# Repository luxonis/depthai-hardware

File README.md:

# DepthAI Open Source Hardware

This repository contains Luxonis open sourced baseboards, including the DepthAI OpenCV AI Kits, and contains Altium design files, documentation, and pictures. This repository is for anyone interested in developing with the OAK SoM or anyone interested in understanding more about the embedded hardware that powers DepthAI. An open source, community KiCad folder is also available for sharing KiCad based designs and components.

The designs are Dual Licensed under [MIT](LICENSE) or [KiCad Libraries License](LICENSE.KiCad.md)

# POE Designs

## [OAK-D-POE | SJ2088POE](https://github.com/luxonis/depthai-hardware/tree/master/SJ2088POE_PoE_Board)

This board is the basis for the OAK-D-POE.  And it is the equivalent of the BW1098OBC/BW1098OAK, but with POE instead of USB.  So 3 onboard cameras (1x onboard IMX378 12MP autofocus color camera, 2x global shutter grayscale for stereo depth), with the stereo baseline being 7.5cm (just like BW1098OBC/BW1098OAK/OAK-D).

This design is in progress.  When complete it will support the DepthAI API over Ethernet, and some additional features like direct RTSP streaming.

## [OAK-1-POE | SJ2096POE](https://github.com/luxonis/depthai-hardware/tree/master/SJ2096POE_R0M0E0)

This is the basis for OAK-1-POE.  It is the equivalent of the BK1096_OAK, with with POE instead of USB.  So 1x onboard IMX378 12MP autofocus color camera.

This design is in progress.  When complete it will support the DepthAI API over Ethernet, and some additional features like direct RTSP streaming.

## [BW2098POE](https://github.com/luxonis/depthai-hardware/tree/master/BW2098POE_PoE_Board)
The [BW2098POE repository](https://github.com/luxonis/depthai-hardware/tree/master/BW2098POE_PoE_Board) contains open hardware designed by Luxonis, and meant to be used as a baseboard for the [Luxonis](https://www.luxonis.com/depthai) BW2099 OAK SoM. The BW2098POE baseboard offers full 802.3af, Class 3 PoE compliance with 1000BASE-T speeds, along with user-selectable external power from a 5V barrel jack. The Luxonis BW0249 12MP RGB camera module can be connected via the 26-pin FFC interface, which exposes a 4-lane MIPI CSI-2 channel directly into the Myriad X on the BW2099 module for processing. Data can also be streamed to a host via USB 3.1 Gen1 (Type-C). Finally, the BW2098POE board exposes boot selection switches, allowing the end user to boot the BW2099 module from USB or the on-board eMMC or NOR flash.

# Integrated Raspberry Pi Designs

## [DM1097](https://github.com/luxonis/depthai-hardware/tree/master/DM1097_DepthAI_Compute_Module_4#dm1097_r0m0e0-depthai-for-compute-module-4)
The [DM1097](https://github.com/luxonis/depthai-hardware/tree/master/DM1097_DepthAI_Compute_Module_4#dm1097_r0m0e0-depthai-for-compute-module-4) contains the design files for DepthAI with an integrated/onboard [Raspberry Pi Compute Module 4](https://www.raspberrypi.org/products/compute-module-4/?variant=raspberry-pi-cm4001000).
The DM1097 combines a host and the Luxonis OAK SoM to allow for fully integrated solution for real-time spatial AI. It is effectively the same as the BW1097, below, but with a Pi 4 computer module instead of a Pi 3 compute module.

## [BW1097](BW1097_DepthAI_Compute_Module)
The [BW1097 repository](/BW1097_DepthAI_Compute_Module) contains open hardware designed by Luxonis, and meant to be used as a baseboard for the [Luxonis](https://www.luxonis.com/depthai) BW1099 OAK SoM and the [Raspberry Pi Compute Module 3+](https://www.raspberrypi.org/products/compute-module-3-plus/). Based on the Raspberry PI CMIO board, the BW1097 combines a host and the Luxonis OAK SoM to allow for fully integrated solution for real-time spatial AI.

# USB Designs

## [OAK-D | BW1098OAK](https://github.com/luxonis/depthai-hardware/tree/master/BW1098OAK_USB3C#bw1098oak-usb3c-baseboard)

This board is used in the depthai product known as the OpenCV AI Kit with Depth, OAK-D:

## [BW1098OBC](BW1098OBC_DepthAI_USB3C)
The [BW1098OBC repository](BW1098OBC_DepthAI_USB3C) contains open hardware designed by Luxonis, and meant to be used as a baseboard for the [Luxonis](https://www.luxonis.com/depthai) BW1099 OAK SoM. The BW1098OBC baseboard has three on-board cameras which implement stereo and RGB vision, piped directly into the OAK SoM for depth and AI processing. The data is then output to a host via USB 3.1 Gen1 (Type-C).

# USB designs with attachable FFC camera boards

The 1090 is our updated version from the common issues customers have had with BW1098FFC. (We will keep selling the 1098FFC, for folks who have that connector type.)
Improvements/changes:

- More robust mechanical connection (a LOT more robust)
- ESD protection added.
- Standardized pinout (All 3 camera connectors have the same pinout - meaning that mix/match can be done using 2x 2-lane MIPI and 1x 4-lane MIPI)
- Capability to use with ArduCam cameras w/out an adapter board (including clock sync and trigger sync).

Below is a flow-chart showing the evolution of this design over time based on customer feedback/needs.

More information about each design can be found in corresponding repositories.

## [DM1090FFC](DM1090FFC_DepthAI_USB3)

The [DM1090FFC repository](DM1090FFC_DepthAI_USB3) contains open hardware designed by Luxonis, and meant to be used as a baseboard for the [Luxonis](https://www.luxonis.com/depthai) BW1099 OAK SoM. The DM1090FFC baseboard has three FFC interfaces which allow for two [DM0250TG](DM0250TG_DepthAI_Mono_Camera) camera modules (stereo pair) and one [DM0249](DM0249_DepthAI_RGB_Camera) RGB camera module.
Besides Luxonis camera modules, several Arducam CCMs can be connected to [DM1090FFC](DM1090FFC_DepthAI_USB3).
Please note that only revision R1 and above (R1M1E1) ([DM0250TG](DM0250TG_DepthAI_Mono_Camera) and [DM0249](DM0249_DepthAI_RGB_Camera)) cameras with 26-pin FFC connectors can be connected to [DM1090FFC](DM1090FFC_DepthAI_USB3).

## [BW1094](BW1094_DepthAI_HAT)
The [BW1094 repository](BW1094_DepthAI_HAT) contains open hardware designed by Luxonis, and meant to be used as a baseboard for the [Luxonis](https://www.luxonis.com/depthai) BW1099 OAK SoM and as a HAT for the [RPi "B" models](https://www.raspberrypi.org/products/). The BW1094 baseboard has three FFC interfaces which allow for two [BG0250TG](BG0250TG_DepthAI_Mono_Camera) camera modules (stereo pair) and one [BG0249](BG0249_DepthAI_RGB_Camera) RGB camera module. The GPIO interface from the Raspberry Pi Model B variants is passed through the BW1094 with the exception of the 5V pins, GND pins, and [BCM GPIO26 (pin 37)](https://www.raspberrypi.org/documentation/usage/gpio/), which is used as a way for the Raspberry Pi to reset the OAK SoM, parallel to the RST button.

## [BK1096](BK1096_OAK-1_Modular)
The [BK1096 repository](/BK1096_OAK-1_Modular) contains open hardware designed by Luxonis, and meant to be used as a baseboard for the [Luxonis](https://www.luxonis.com/depthai) BW1099 OAK SoM. The BK1096 baseboard offers a quick and simple way to add USB3 Type-C device power and connectivity, and a single 12MP RGB camera module to the OAK SoM.

# Cameras and Camera Adapter Boards

## [BG0249](BG0249_DepthAI_RGB_Camera)
The [BG0249 repository](BG0249_DepthAI_RGB_Camera) contains open hardware designed by Luxonis. The BW0249 is a carrier board for the Sunny A12N02A IMX378 camera module, and is designed to be compatible with the [BW1094](BW1094_DepthAI_HAT) and [BW1098FFC](BW1098FFC_DepthAI_USB3) baseboards. A 26-pin FFC is used to carry 5V power, 4-lane MIPI, I2C, and other control signals between the BW0249 and the controller baseboards.

## [BG0250TG](BG0250TG_DepthAI_Mono_Camera)
The [BG0250TG repository](BG0250TG_DepthAI_Mono_Camera) contains open hardware designed by Luxonis. The BW0250TG is a carrier board for the Sunny TG161B or AN01V32 OV9282 camera module, and is designed to be compatible with the [BW1094](BW1094_DepthAI_HAT) and [BW1098FFC](BW1098FFC_DepthAI_USB3) baseboards. A 20-pin FFC is used to carry 5V power, 2-lane MIPI, I2C, and other control signals between the BW0250TG and the controller baseboards. A single BG0250TG is typically paired with another to create a stereo camera pair.

## [BW0253_R0M0E0 Raspberry Pi HQ Cam Adapter Board](/BW0253_R0M0E0_RPIHQ_ADAPTER)

The [BW0253_R0M0E0](/BW0253_R0M0E0_RPIHQ_ADAPTER) is an adapter board to allow the [Raspberry Pi HQ camera](https://www.raspberrypi.org/products/raspberry-pi-high-quality-camera/) to physically interface to the DepthAI RGB camera port on the [BW1098FFC](https://github.com/luxonis/depthai-hardware/tree/master/BW1098FFC_DepthAI_USB3).

This allows using DepthAI with all sorts of lens combinations, including variable zoom, variable focus, and even [with a telescope](https://www.tomshardware.com/news/raspberry-pi-high-quality-camera-used-for-out-of-this-world-astrophotography).

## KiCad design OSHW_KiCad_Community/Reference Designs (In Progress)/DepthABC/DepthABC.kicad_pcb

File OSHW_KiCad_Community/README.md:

# DepthAI Open Source Hardware KiCad Community

An open source, community KiCad folder is also available for sharing KiCad based designs and components. 

## Contents

### Footprints

Contains entire *converted* altium luxonis-depthAI footprint library. Dimensions unconfirmed where noted. As they are checked they should be placed into the master library. Same goes for any footprints you create for a depthAI related design. 

### Schematic Libraries

Kicad depthAI schematic symbols. All are correct, some are missing, many have not had their footprint checked and assigned (but all are available in footprints). Still, use KiCad libraries if you have the part - will already have a model and footprint associated. 

### Reference Designs (in progress)

For KiCad versions of the reference designs provided in altium or their derivatives. Contains complete BW1098OBC-USBC Schematic as well as the WIP BW1098-ABC, a new collaboration with Chris Gammell.

### SoMs
this folder contains work on the 100 pin SoM connector using v6 of KiCad. The footprints folder and schematic libraries folders have it for v5. Going forward save v6 symbols with _v6 at the end so they can be differentiated (kicad v5 cannot use v6 footprints and symbols)
-->still need BW2099 Symbol
### Note: 

KiCad versions of reference designs, footprint/schematic libraries are still very much in the early stages. Once a few designs are complete and more footprints are confirmed, etc, it will be noted which parts of this directory are complete and may be used for reference while others will be marked WIP. For now assume all subdirectories to be in progress unless otherwise noted but please feel free to fork and add what you can to help out with the depthAI community.

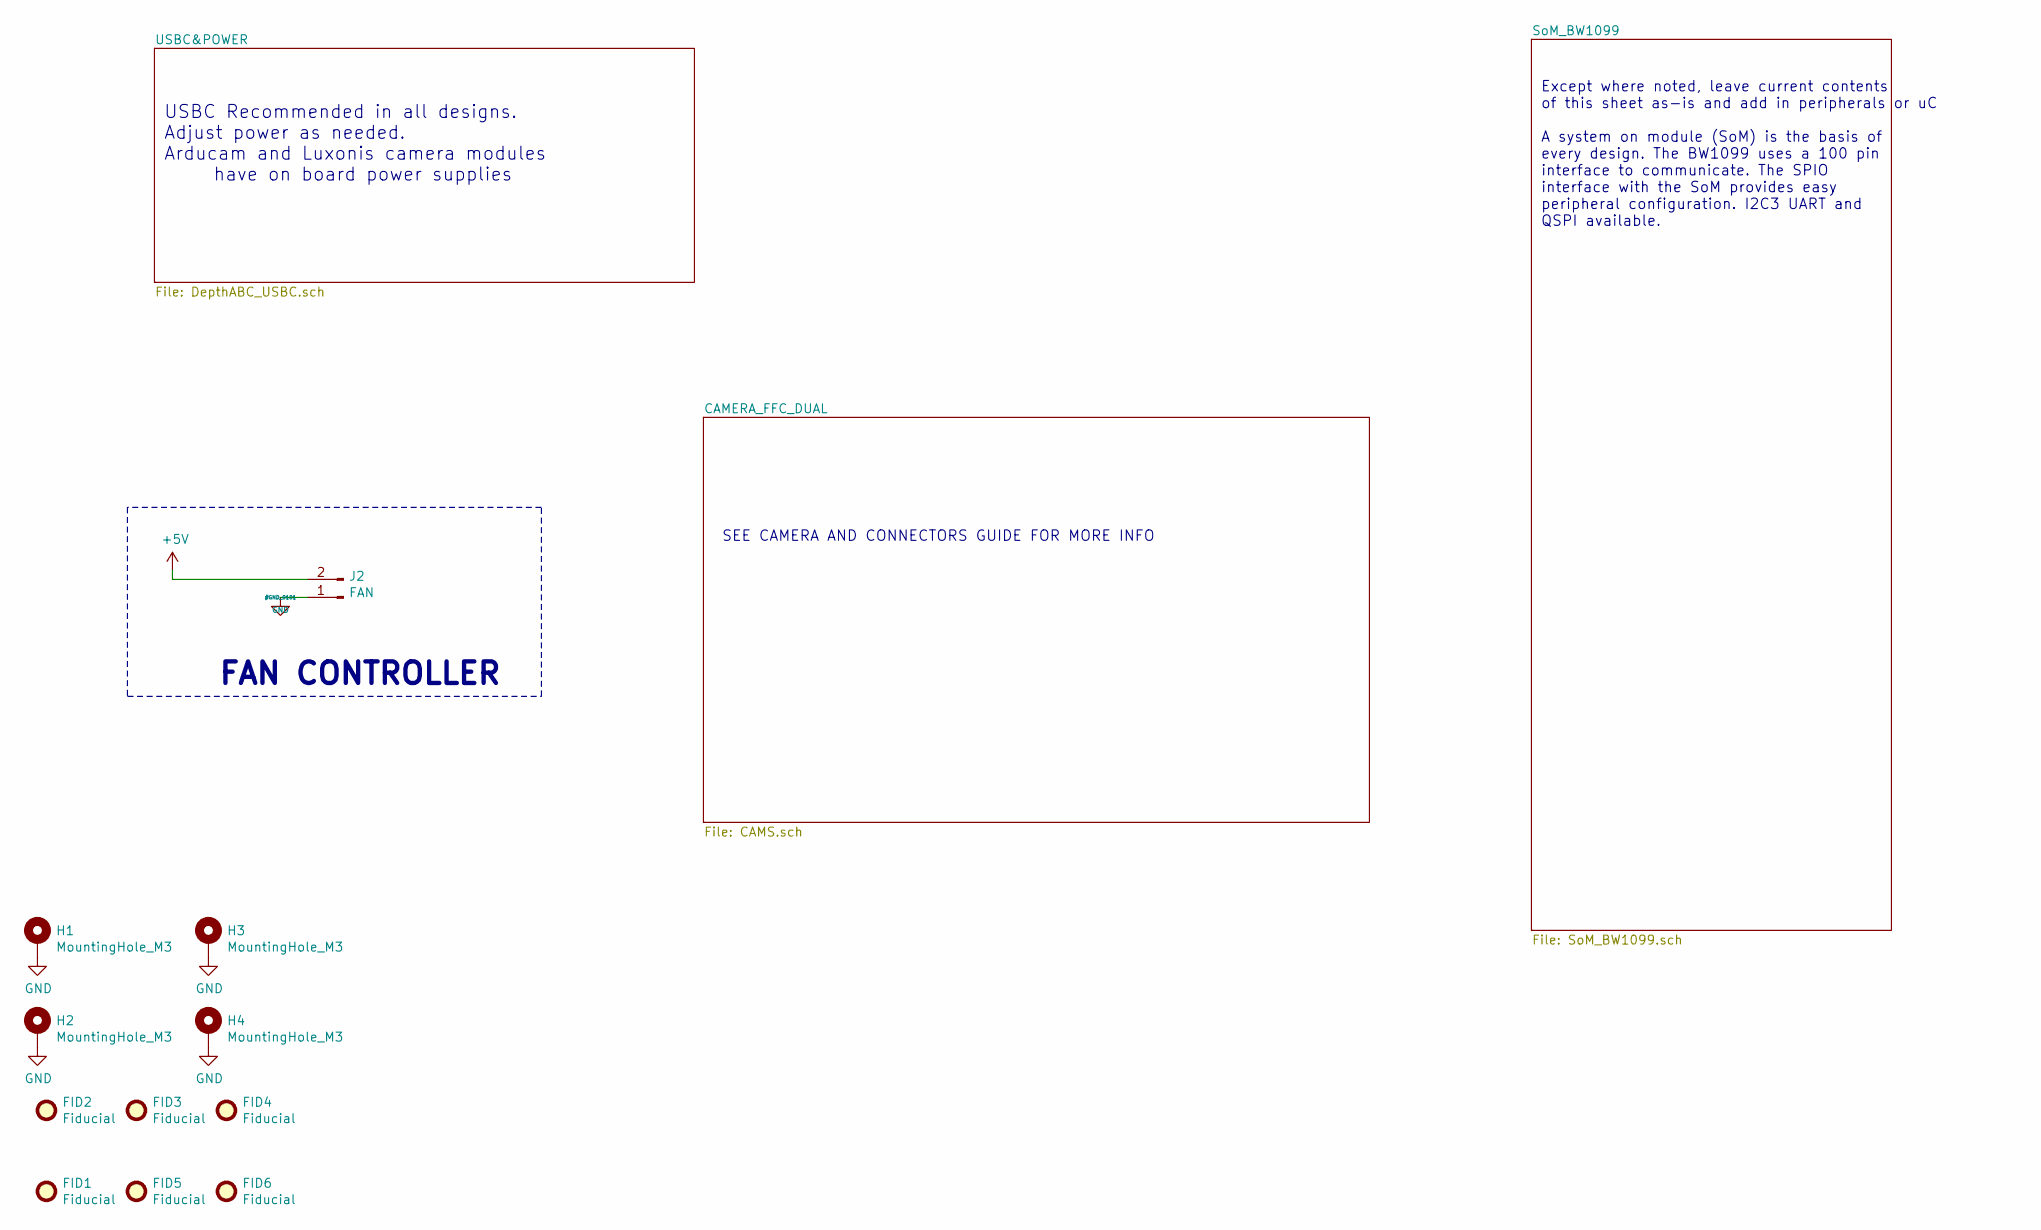
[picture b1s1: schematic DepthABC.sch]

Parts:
FID1, FID2, FID3, FID4, FID5, FID6: Fiducial; Fiducial_1mm_Mask2mm
H1, H2, H3, H4: MountingHole_M3; MountingHole_3.2mm_M3_ISO7380_Pad
J2: FAN; PinHeader_1x02_P2.54mm_Vertical

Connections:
+5V: J2.2; also elsewhere on the board

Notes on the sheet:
SEE CAMERA AND CONNECTORS GUIDE FOR MORE INFO
Except where noted, leave current contents of this sheet as-is and add in peripherals or uC A system on module (SoM) is the basis of every design. The BW1099 uses a 100 pin interface to communicate. The SPIO interface with the SoM provides easy peripheral configuration. I2C3 UART and QSPI available.
USBC Recommended in all designs. Adjust power as needed. Arducam and Luxonis camera modules have on board power supplies
FAN CONTROLLER

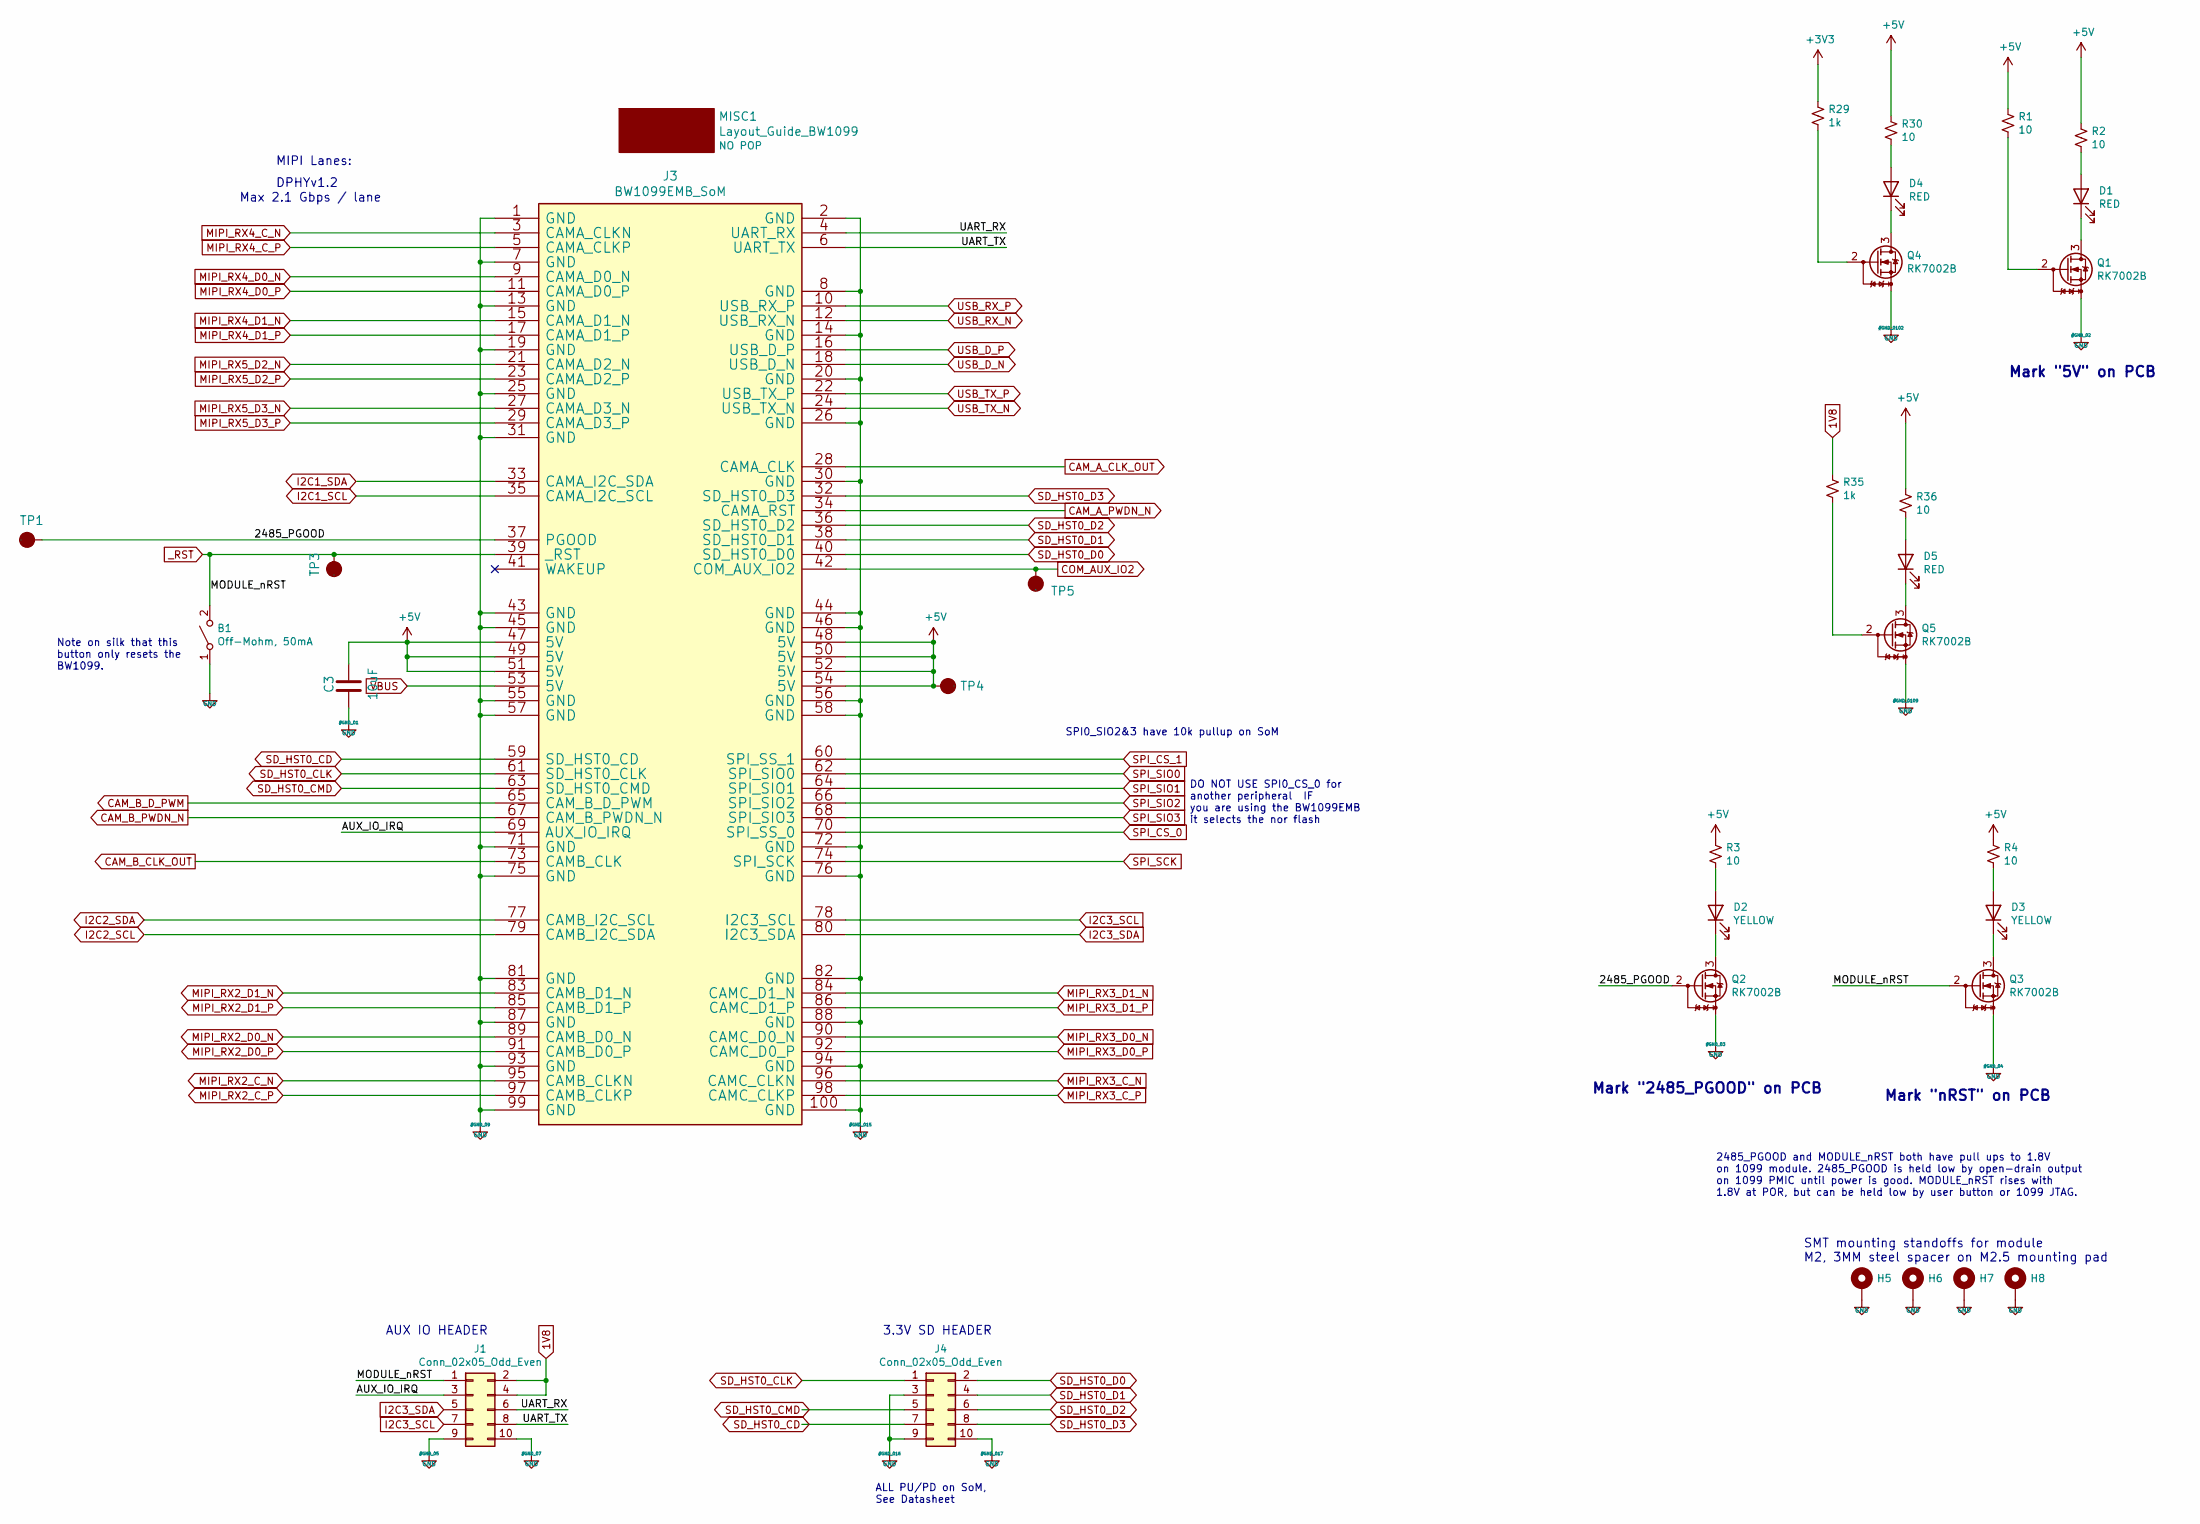
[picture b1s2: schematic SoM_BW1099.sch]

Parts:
B1: Off-Mohm, 50mA; SW_PTS636_SM43J_SMTR_LFS; MPN1 PTS636
C3: 10uF; C_0603_1608Metric; Voltage Rating 6.3V; MPN1 C0603C106M8PAC7867
D1, D4, D5: RED; LED_0805_2012Metric; MPN1 APT2012SRCPRV
D2, D3: YELLOW; LED_0805_2012Metric; MPN1 APT2012SYCK/J3-PRV
H5, H6, H7, H8: MountingHole_Pad; Mounting_Wuerth_WA-SMSI-M2_H3mm_9774030243; MPN1 9774030243R
J1, J4: Conn_02x05_Odd_Even; PinSocket_2x05_P2.54mm_Vertical_SMD
J3: BW1099EMB_SoM; DF40HC(3.0)-100DS-0.4V(58); MPN1 DF40HC(3.0)-100DS-0.4V(58)
MISC1: Layout_Guide_BW1099; BW1099_Layout_Guide
Q1, Q2, Q3, Q4, Q5: RK7002B; SOT-23; Voltage Rating 60V 250mA
R1, R2, R3, R4, R30, R36: 10; R_0603_1608Metric; Voltage Rating 1/10W; MPN1 ESR03EZPF10R0
R29, R35: 1k; R_0603_1608Metric; Voltage Rating 1/10W; MPN1 SG73S1JTTD1001F
TP1, TP3, TP4, TP5: TestPoint_Pad_D2.0mm

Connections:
1V8: J1.2, J1.4, R35.1; also elsewhere on the board
+5V: C3.2, J3.47 (5V), J3.48 (5V), J3.49 (5V), J3.50 (5V), J3.51 (5V), J3.52 (5V), J3.54 (5V), R1.1, R2.1, R3.1, R4.1, R30.1, R36.1, TP4.1; also elsewhere on the board
/SoM_BW1099/2485_PGOOD: J3.37 (PGOOD), Q2.2 (G), TP1.1
/SoM_BW1099/AUX_IO_IRQ: J1.3, J3.69 (AUX_IO_IRQ)
/SoM_BW1099/UART_RX: J1.6, J3.4 (UART_RX)
/SoM_BW1099/UART_TX: J1.8, J3.6 (UART_TX)
CAM_A_CLK_OUT: J3.28 (CAMA_CLK); also elsewhere on the board
CAM_A_PWDN_N: J3.34 (CAMA_RST); also elsewhere on the board
CAM_B_CLK_OUT: J3.73 (CAMB_CLK); also elsewhere on the board
CAM_B_D_PWM: J3.65 (CAM_B_D_PWM); also elsewhere on the board
CAM_B_PWDN_N: J3.67 (CAM_B_PWDN_N); also elsewhere on the board
COM_AUX_IO2: J3.42 (COM_AUX_IO2), TP5.1; also elsewhere on the board
I2C1_SCL: J3.35 (CAMA_I2C_SCL); also elsewhere on the board
I2C1_SDA: J3.33 (CAMA_I2C_SDA); also elsewhere on the board
I2C2_SCL: J3.79 (CAMB_I2C_SDA); also elsewhere on the board
I2C2_SDA: J3.77 (CAMB_I2C_SCL); also elsewhere on the board
I2C3_SCL: J1.7, J3.78 (I2C3_SCL)
I2C3_SDA: J1.5, J3.80 (I2C3_SDA)
MIPI_RX2_C_N: J3.95 (CAMB_CLKN); also elsewhere on the board
MIPI_RX2_C_P: J3.97 (CAMB_CLKP); also elsewhere on the board
MIPI_RX2_D0_N: J3.89 (CAMB_D0_N); also elsewhere on the board
MIPI_RX2_D0_P: J3.91 (CAMB_D0_P); also elsewhere on the board
MIPI_RX2_D1_N: J3.83 (CAMB_D1_N); also elsewhere on the board
MIPI_RX2_D1_P: J3.85 (CAMB_D1_P); also elsewhere on the board
MIPI_RX3_C_N: J3.96 (CAMC_CLKN); also elsewhere on the board
MIPI_RX3_C_P: J3.98 (CAMC_CLKP); also elsewhere on the board
MIPI_RX3_D0_N: J3.90 (CAMC_D0_N); also elsewhere on the board
MIPI_RX3_D0_P: J3.92 (CAMC_D0_P); also elsewhere on the board
MIPI_RX3_D1_N: J3.84 (CAMC_D1_N); also elsewhere on the board
MIPI_RX3_D1_P: J3.86 (CAMC_D1_P); also elsewhere on the board
MIPI_RX4_C_N: J3.3 (CAMA_CLKN); also elsewhere on the board
MIPI_RX4_C_P: J3.5 (CAMA_CLKP); also elsewhere on the board
MIPI_RX4_D0_N: J3.9 (CAMA_D0_N); also elsewhere on the board
MIPI_RX4_D0_P: J3.11 (CAMA_D0_P); also elsewhere on the board
MIPI_RX4_D1_N: J3.15 (CAMA_D1_N); also elsewhere on the board
MIPI_RX4_D1_P: J3.17 (CAMA_D1_P); also elsewhere on the board
MIPI_RX5_D2_N: J3.21 (CAMA_D2_N); also elsewhere on the board
MIPI_RX5_D2_P: J3.23 (CAMA_D2_P); also elsewhere on the board
MIPI_RX5_D3_N: J3.27 (CAMA_D3_N); also elsewhere on the board
MIPI_RX5_D3_P: J3.29 (CAMA_D3_P); also elsewhere on the board
unnamed: D1.1 (K), Q1.3 (D)
unnamed: D1.2 (A), R2.2
unnamed: D2.1 (K), Q2.3 (D)
unnamed: D2.2 (A), R3.2
unnamed: D3.1 (K), Q3.3 (D)
unnamed: D3.2 (A), R4.2
unnamed: D4.1 (K), Q4.3 (D)
unnamed: D4.2 (A), R30.2
unnamed: D5.1 (K), Q5.3 (D)
unnamed: D5.2 (A), R36.2
unnamed: Q1.2 (G), R1.2
unnamed: Q4.2 (G), R29.2
unnamed: Q5.2 (G), R35.2
SD_HST0_CD: J3.59 (SD_HST0_CD), J4.7; also elsewhere on the board
SD_HST0_CLK: J3.61 (SD_HST0_CLK), J4.1; also elsewhere on the board
SD_HST0_CMD: J3.63 (SD_HST0_CMD), J4.5; also elsewhere on the board
SD_HST0_D0: J3.40 (SD_HST0_D0), J4.2; also elsewhere on the board
SD_HST0_D1: J3.38 (SD_HST0_D1), J4.4; also elsewhere on the board
SD_HST0_D2: J3.36 (SD_HST0_D2), J4.6; also elsewhere on the board
SD_HST0_D3: J3.32 (SD_HST0_D3), J4.8; also elsewhere on the board
SPI_CS_0: J3.70 (SPI_SS_0); also elsewhere on the board
SPI_CS_1: J3.60 (SPI_SS_1); also elsewhere on the board
SPI_SCK: J3.74 (SPI_SCK); also elsewhere on the board
SPI_SIO0: J3.62 (SPI_SIO0); also elsewhere on the board
SPI_SIO1: J3.64 (SPI_SIO1); also elsewhere on the board
SPI_SIO2: J3.66 (SPI_SIO2); also elsewhere on the board
SPI_SIO3: J3.68 (SPI_SIO3); also elsewhere on the board
USB_D_N: J3.18 (USB_D_N); also elsewhere on the board
USB_D_P: J3.16 (USB_D_P); also elsewhere on the board
USB_RX_N: J3.12 (USB_RX_N); also elsewhere on the board
USB_RX_P: J3.10 (USB_RX_P); also elsewhere on the board
USB_TX_N: J3.24 (USB_TX_N); also elsewhere on the board
USB_TX_P: J3.22 (USB_TX_P); also elsewhere on the board
VBUS: J3.53 (5V); also elsewhere on the board
_RST: B1.2 (B), J1.1, J3.39 (_RST), Q3.2 (G), TP3.1; also elsewhere on the board

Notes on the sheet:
SMT mounting standoffs for module M2, 3MM steel spacer on M2.5 mounting pad
Mark "5V" on PCB
Mark "2485_PGOOD" on PCB
Mark "nRST" on PCB
AUX IO HEADER
3.3V SD HEADER
Note on silk that this button only resets the BW1099.
2485_PGOOD and MODULE_nRST both have pull ups to 1.8V on 1099 module. 2485_PGOOD is held low by open-drain output on 1099 PMIC until power is good. MODULE_nRST rises with 1.8V at POR, but can be held low by user button or 1099 JTAG.
DPHYv1.2
MIPI Lanes:
Max 2.1 Gbps / lane
SPI0_SIO2&3 have 10k pullup on SoM
DO NOT USE SPI0_CS_0 for another peripheral IF you are using the BW1099EMB it selects the nor flash
ALL PU/PD on SoM, See Datasheet

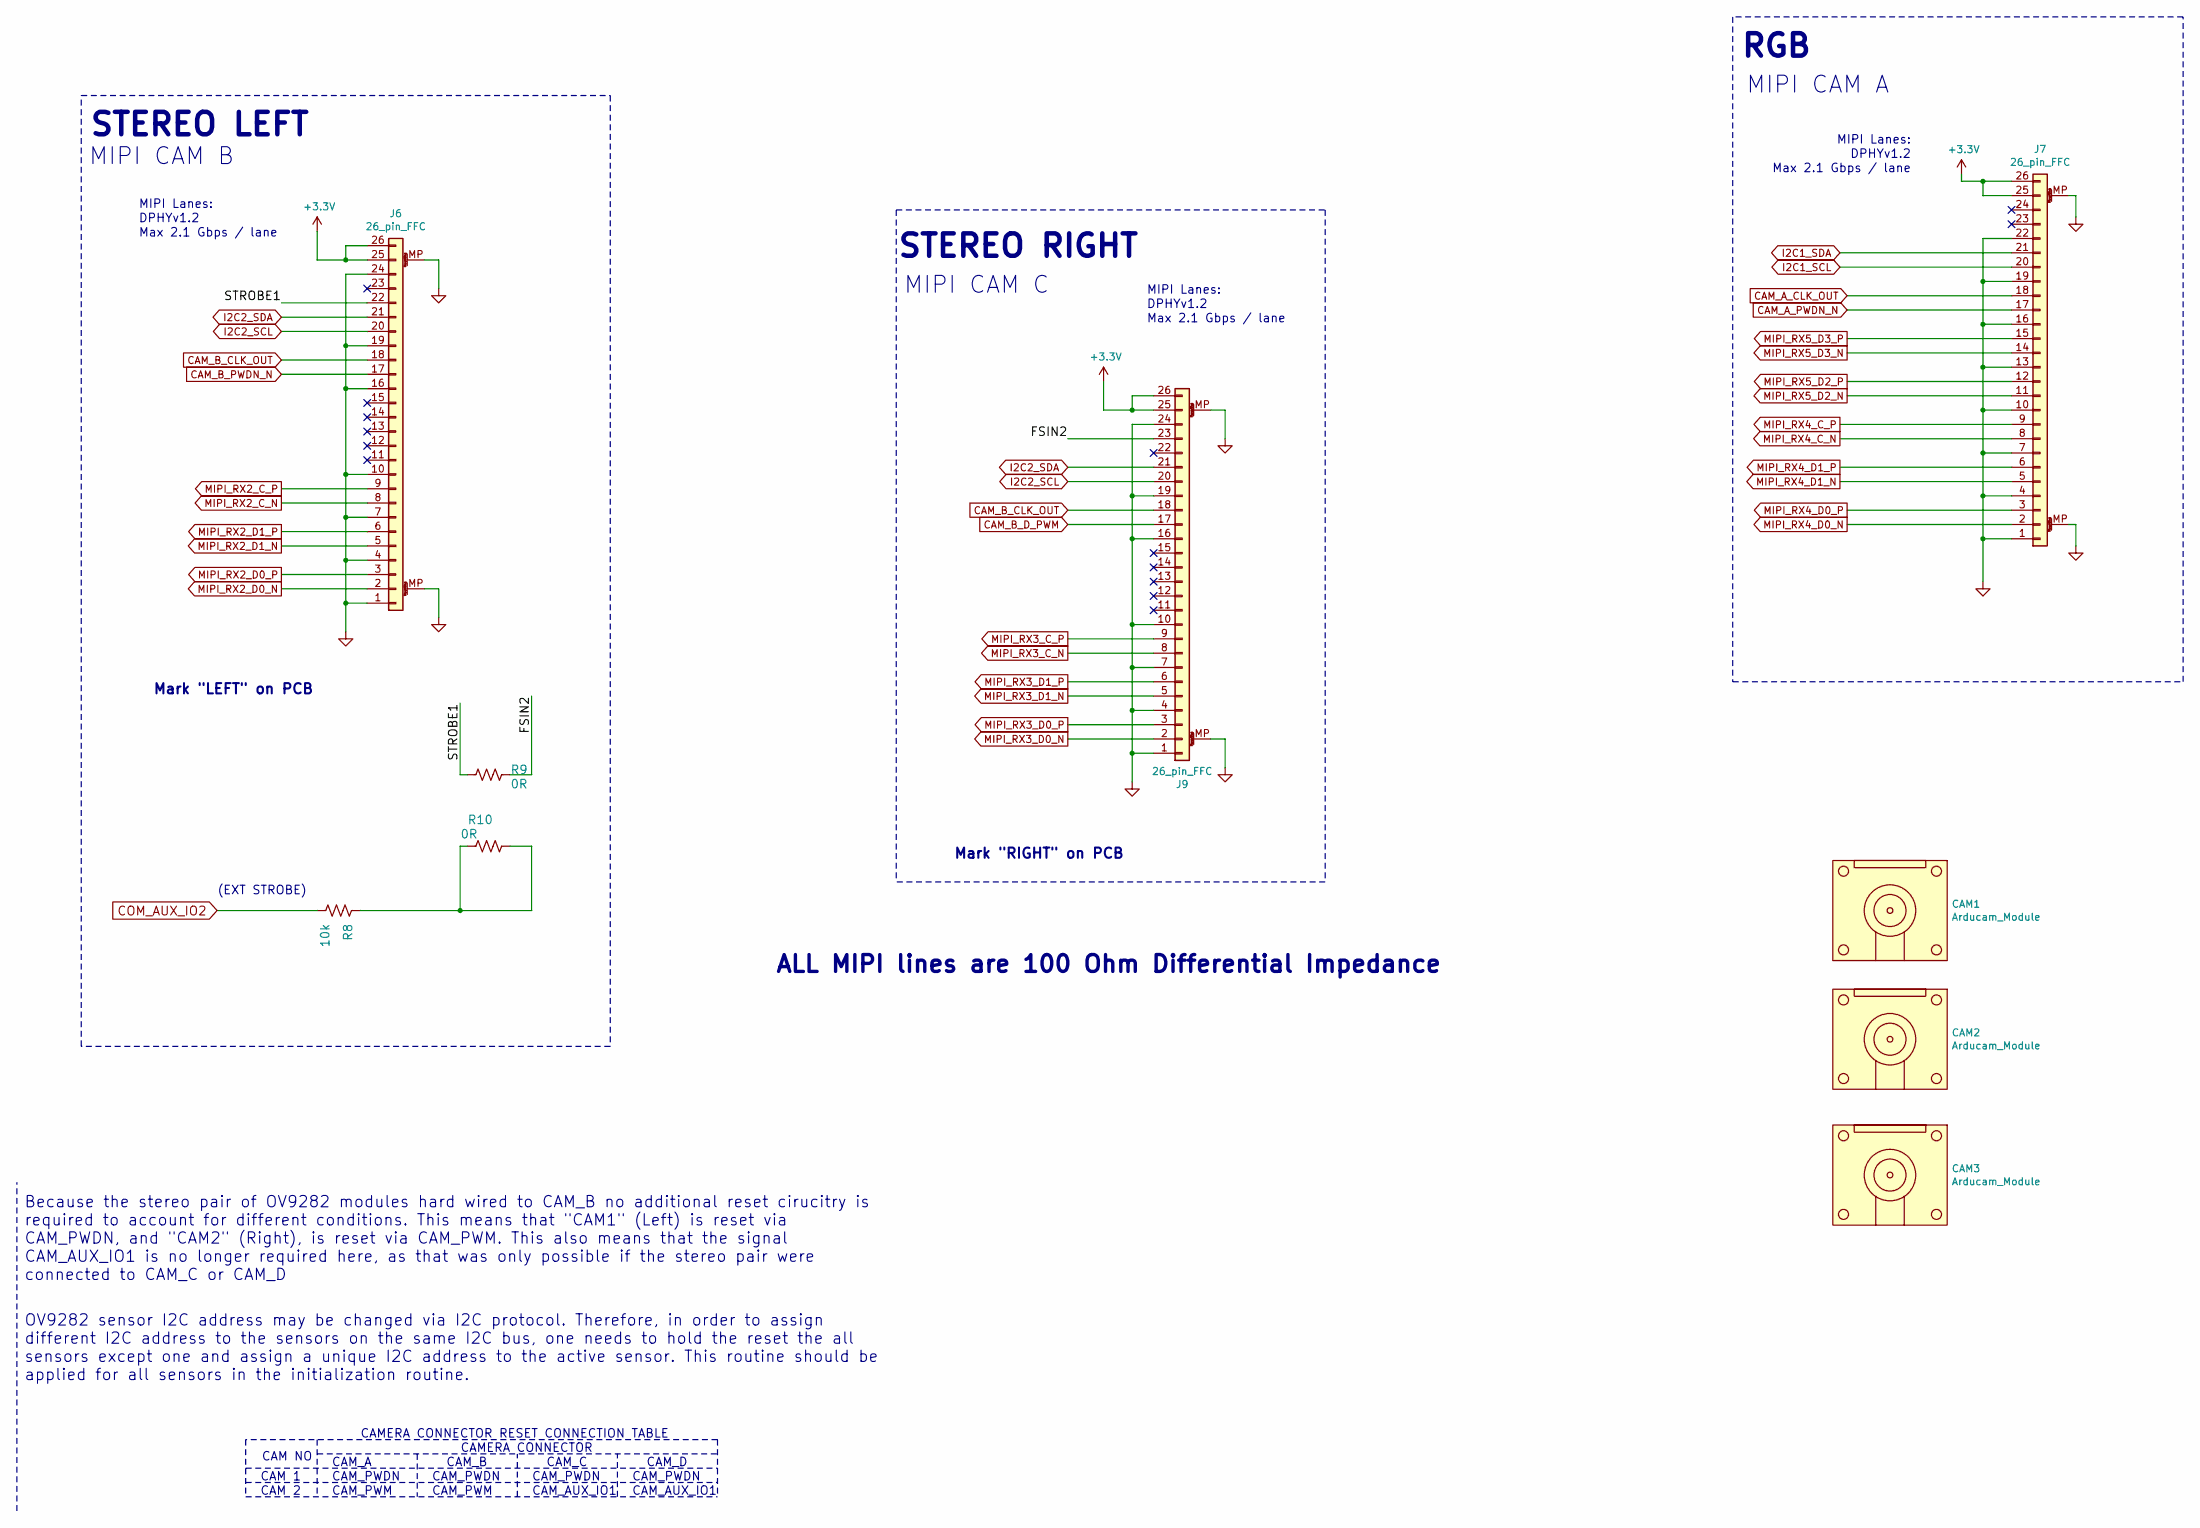
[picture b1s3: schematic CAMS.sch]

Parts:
CAM1, CAM2, CAM3: Arducam_Module; arducam_40mm_34mm
J6, J7, J9: 26_pin_FFC; F32R-26p-FFC; MPN1 F32R-1A7H1-11026
R8: 10k; R_0603_1608Metric; Voltage Rating 1/10W; MPN1 RC0603FR-7W10KL
R9, R10: 0R; R_0603_1608Metric; Voltage Rating 1/10W; MPN1 RC0603FR-070RL

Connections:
/CAMERA_FFC_DUAL/FSIN2: J9.23, R9.1
/CAMERA_FFC_DUAL/STROBE1: J6.22, R9.2
CAM_A_CLK_OUT: J7.18; also elsewhere on the board
CAM_A_PWDN_N: J7.17; also elsewhere on the board
CAM_B_CLK_OUT: J6.18, J9.18; also elsewhere on the board
CAM_B_D_PWM: J9.17; also elsewhere on the board
CAM_B_PWDN_N: J6.17; also elsewhere on the board
COM_AUX_IO2: R8.2; also elsewhere on the board
I2C1_SCL: J7.20; also elsewhere on the board
I2C1_SDA: J7.21; also elsewhere on the board
I2C2_SCL: J6.20, J9.20; also elsewhere on the board
I2C2_SDA: J6.21, J9.21; also elsewhere on the board
MIPI_RX2_C_N: J6.8; also elsewhere on the board
MIPI_RX2_C_P: J6.9; also elsewhere on the board
MIPI_RX2_D0_N: J6.2; also elsewhere on the board
MIPI_RX2_D0_P: J6.3; also elsewhere on the board
MIPI_RX2_D1_N: J6.5; also elsewhere on the board
MIPI_RX2_D1_P: J6.6; also elsewhere on the board
MIPI_RX3_C_N: J9.8; also elsewhere on the board
MIPI_RX3_C_P: J9.9; also elsewhere on the board
MIPI_RX3_D0_N: J9.2; also elsewhere on the board
MIPI_RX3_D0_P: J9.3; also elsewhere on the board
MIPI_RX3_D1_N: J9.5; also elsewhere on the board
MIPI_RX3_D1_P: J9.6; also elsewhere on the board
MIPI_RX4_C_N: J7.8; also elsewhere on the board
MIPI_RX4_C_P: J7.9; also elsewhere on the board
MIPI_RX4_D0_N: J7.2; also elsewhere on the board
MIPI_RX4_D0_P: J7.3; also elsewhere on the board
MIPI_RX4_D1_N: J7.5; also elsewhere on the board
MIPI_RX4_D1_P: J7.6; also elsewhere on the board
MIPI_RX5_D2_N: J7.11; also elsewhere on the board
MIPI_RX5_D2_P: J7.12; also elsewhere on the board
MIPI_RX5_D3_N: J7.14; also elsewhere on the board
MIPI_RX5_D3_P: J7.15; also elsewhere on the board
unnamed: R8.1, R10.1, R10.2

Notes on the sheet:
Mark "LEFT" on PCB
CAM NO
CAM 1
CAM 2
CAM_A
CAMERA CONNECTOR
CAM_PWDN
CAM_PWM
CAM_AUX_IO1
CAM_B
CAM_C
CAM_D
CAMERA CONNECTOR RESET CONNECTION TABLE
STEREO LEFT
(EXT STROBE)
OV9282 sensor I2C address may be changed via I2C protocol. Therefore, in order to assign different I2C address to the sensors on the same I2C bus, one needs to hold the reset the all sensors except one and assign a unique I2C address to the active sensor. This routine should be applied for all sens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
Because the stereo pair of OV9282 modules hard wired to CAM_B no additional reset cirucitry is required to account for different conditions. This means that "CAM1" (Left) is reset via CAM_PWDN, and "CAM2" (Right), is reset via CAM_PWM. This also means that the signal CAM_AUX_IO1 is no longer requir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
MIPI CAM B
DPHYv1.2
Max 2.1 Gbps / lane
MIPI Lanes:
STEREO RIGHT
Mark "RIGHT" on PCB
MIPI CAM C
MIPI CAM A
RGB
ALL MIPI lines are 100 Ohm Differential Impedance

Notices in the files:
README.md:
License: MIT
